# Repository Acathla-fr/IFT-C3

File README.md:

# IFT-C3
Printed Circuit Board with an ESP32-C3. Version 2.1 (2024)

Version released for the new students. Now integrates the support for the OLED screen and the buttons.

BUGS!!! (fixed in the kicad design, not on the produced boards):

    Buttons pinout is wrong, you'll have to solder them rotated 25°. For the Boot/Start button, since I thought there was two buttons in one without verifying, you'll have to be creative to fix it (at least the start button, the boot can be selected with Dupont wires by connecting pin 9 to ground).
    Holes for the screen are too small, you'll have to replace the connector or be creative (file the pins works).

GPIO 0 is used by the keyboard matrix<br/>
GPIO 1 is used by the keyboard matrix and optionnaly for battery voltage measurement<br/>
GPIO 2 and 3 are optionnaly used for audio<br/>
GPIO 4 is optionnaly used for the light sensor or to control the MOSFET<br/>
GPIO 5 is used by the SDA line for the OLED screen<br/>
GPIO 6 is used by the SCL line for the OLED screen<br/>
GPIO 7 is used by the keyboard matrix<br/>
GPIO 8 is used by the keyboard matrix<br/>
GPIO 9 is plugged to the Boot button which can be used in your design. The reset button cannot.<br/>
GPIO 9 also optionnaly used for the RGBW LEDs<br/>
GPIO 10 is used by the keyboard matrix<br/>
GPIO 20 is used by the keyboard matrix but also as the Rx UART
GPIO 21 is used by Tx UART

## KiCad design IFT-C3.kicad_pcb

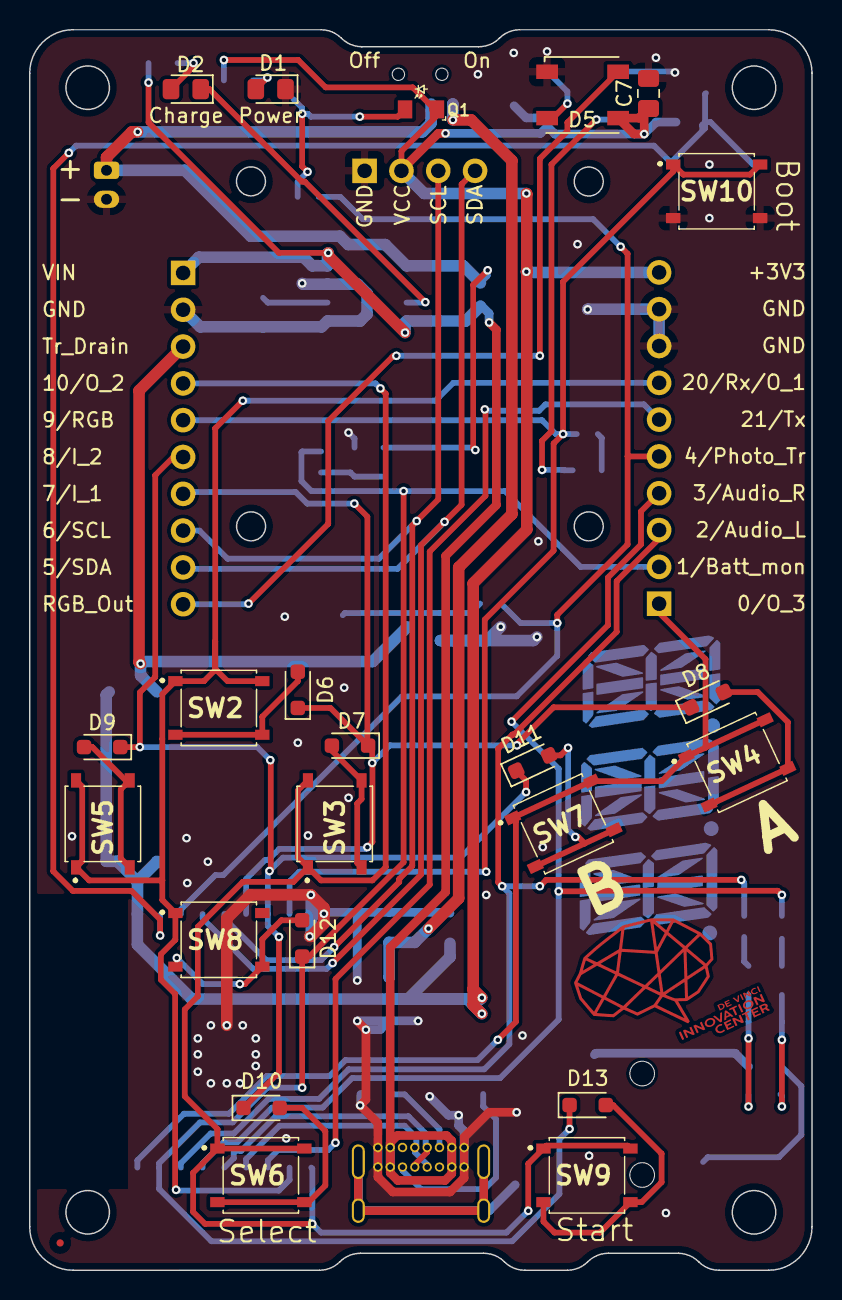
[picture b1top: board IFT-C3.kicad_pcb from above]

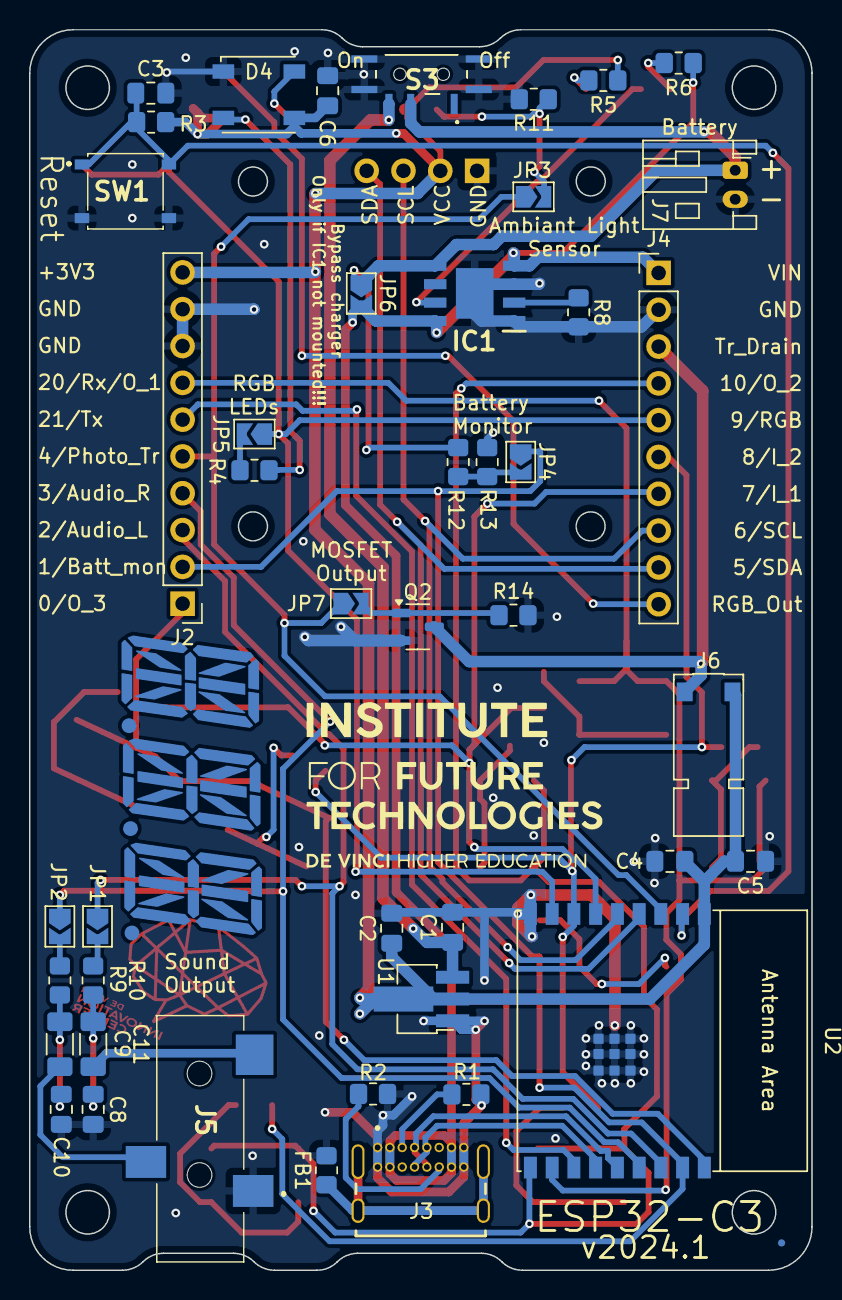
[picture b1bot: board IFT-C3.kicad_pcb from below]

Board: 2 copper layers, 54.0 x 85.6 mm, 70 parts (47 on the bottom side), 50 nets.

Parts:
C1, C2: 22u; C_0805_2012Metric_Pad1.18x1.45mm_HandSolder
C3: 1u; C_0805_2012Metric_Pad1.18x1.45mm_HandSolder
C4, C6, C7: 10u; C_0805_2012Metric_Pad1.18x1.45mm_HandSolder
C5, C8, C10: 100n; C_0805_2012Metric_Pad1.18x1.45mm_HandSolder
C9, C11: 100u; R_1206_3216Metric_Pad1.30x1.75mm_HandSolder
D1, D2: LED; D_0805_2012Metric_Pad1.15x1.40mm_HandSolder
D4, D5: Inolux_IN-PI554FCH; LED_Inolux_IN-PI554FCH_PLCC4_5.0x5.0mm_P3.2mm
D6, D7, D8, D9, D10, D11, D12, D13: 1N4148WS; D_SOD-323_HandSoldering
FB1: FerriteBead; R_0805_2012Metric_Pad1.20x1.40mm_HandSolder
G001, G001#2, G001#3: LOGO; segments
IC1: DIO5508XS8; SOIC127P600X170-9N
J1: Conn_01x04_Socket; SSD1306_module
J2, J4: Conn_01x10_Pin; PinHeader_1x10_P2.54mm_Vertical
J3: USB4085-GF-A_REVB; GCT_USB4085-GF-A_REVB
J5: SJ-3523-SMT-TR; SJ3523SMTTR
J6: Conn_01x02_Pin; Vybronics_VZ30C1T8219732L
J7: Conn_01x02; JST_PH_S2B-PH-K_1x02_P2.00mm_Horizontal
JP1, JP2, JP3, JP4, JP5, JP6, JP7: SolderJumper_2_Open; SolderJumper-2_P1.3mm_Open_TrianglePad1.0x1.5mm
Q1: Q_Photo_NPN; SFH3710
Q2: Q_NMOS_GSD; SOT-23-3
R1, R2: 5.1K; R_0805_2012Metric_Pad1.20x1.40mm_HandSolder
R3, R6, R12, R13, R14: 10K; R_0805_2012Metric_Pad1.20x1.40mm_HandSolder
R4: 330; R_0805_2012Metric_Pad1.20x1.40mm_HandSolder
R5: 1K; R_0805_2012Metric_Pad1.20x1.40mm_HandSolder
R8: 2K; R_0805_2012Metric_Pad1.20x1.40mm_HandSolder
R9, R10: 2.2K; R_0805_2012Metric_Pad1.20x1.40mm_HandSolder
R11: 1M; R_0805_2012Metric_Pad1.20x1.40mm_HandSolder
S3: MSK12C02
SW1, SW2, SW3, SW4, SW5, SW6, SW7, SW8, SW9, SW10: PTS526_SK15_SMTR2_LFS; PTS526SK15SMTR2LFS
U1: AZ1117CR-3.3TRG1; SOT-89-3_Handsoldering
U2: ESP32-C3-WROOM-02

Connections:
+3.3V: C2.1, C4.1, C5.1, C6.1, C7.1, D4.3 (VDD), D5.3 (VDD), J1.2, J2.10, J6.2, Q1.1 (C), R3.2, R5.1, U1.2 (VO), U2.1 (3V3)
+BATT: IC1.5 (BAT), J7.1, JP6.1 (A), R12.1, S3.B1 (COM)
+BATT_after_switch: C1.1, S3.C1 (NO), U1.3 (VI)
/Charge: D2.1 (K), IC1.7 (CHRGB)
/D+: J3.A6 (DP1), J3.B6 (DP2), U2.14 (GPIO19/USB_D+)
/D-: J3.A7 (DN1), J3.B7 (DN2), U2.13 (GPIO18/USB_D-)
/PWM_filter1/In: JP2.2 (B), R10.2
/PWM_filter1/Out: C11.2, J5.3 (RING)
/PWM_filter/In: JP1.2 (B), R9.2
/PWM_filter/Out: C9.2, J5.2 (TIP)
/RGB_OUT: D5.4 (DO), J4.10
/Tx: J2.6, U2.12 (GPIO21/U0TXD)
Audio_L: J2.3, JP1.1 (A), U2.16 (GPIO2/ADC1_CH2)
Audio_R: J2.4, JP2.1 (A), U2.15 (GPIO3/ADC1_CH3)
Batt_mon: D12.1 (K), D13.1 (K), J2.2, JP4.1 (A), U2.17 (GPIO1/ADC1_CH1/XTAL_32K_N)
GND: C1.2, C2.2, C3.2, C4.2, C5.2, C6.2, C7.2, C8.2, C10.2, D1.1 (K), D4.1 (VSS), D5.1 (VSS), FB1.2, IC1.1 (TEMP), IC1.3 (GND), IC1.9 (EP), J1.1, J2.8, J2.9, J3.A1 (GND), J3.A12 (GND), J3.B1 (GND), J3.B12 (GND), J4.2, J5.1 (SLEEVE), J7.2, Q2.2 (S), R1.1, R2.2, R8.1, R11.2, R13.2, R14.2, S3.MP1, S3.MP2, S3.MP3, S3.MP4, SW1.3, SW1.4, SW10.3, SW10.4, U1.1 (GND), U2.9 (GND), U2.19 (GND)
I_1: D6.1 (K), D7.1 (K), D8.1 (K), J4.7, U2.6 (GPIO7)
I_2: D9.1 (K), D10.1 (K), D11.1 (K), J4.6, U2.7 (GPIO8)
unnamed: C8.1, C9.1, R9.1
unnamed: C10.1, C11.1, R10.1
unnamed: D1.2 (A), R5.2
unnamed: D2.2 (A), R6.2
unnamed: D4.2 (DIN), R4.1
unnamed: D4.4 (DO), D5.2 (DIN)
unnamed: D6.2 (A), SW2.3, SW2.4
unnamed: D7.2 (A), SW3.3, SW3.4
unnamed: D8.2 (A), SW4.3, SW4.4
unnamed: D9.2 (A), SW5.3, SW5.4
unnamed: D10.2 (A), SW6.3, SW6.4
unnamed: D11.2 (A), SW7.3, SW7.4
unnamed: D12.2 (A), SW8.3, SW8.4
unnamed: D13.2 (A), SW9.3, SW9.4
unnamed: FB1.1, J3.S1 (SHELL), J3.S2 (SHELL), J3.S3 (SHELL), J3.S4 (SHELL)
unnamed: IC1.2 (PROG), R8.2
unnamed: J3.A5 (CC1), R1.2
unnamed: J3.B5 (CC2), R2.1
unnamed: JP3.2 (B), Q1.2 (E), R11.1
unnamed: JP4.2 (B), R12.2, R13.1
unnamed: JP5.2 (B), R4.2
unnamed: JP7.2 (B), Q2.1 (G), R14.1
unnamed: C3.1, R3.1, SW1.1, SW1.2, U2.2 (EN/CHIP_PU)
O_1: J2.7, SW2.1, SW2.2, SW5.1, SW5.2, SW8.1, SW8.2, U2.11 (GPIO20/U0RXD)
O_2: J4.4, SW3.1, SW3.2, SW6.1, SW6.2, SW9.1, SW9.2, U2.10 (GPIO10)
O_3: J2.1, SW4.1, SW4.2, SW7.1, SW7.2, U2.18 (GPIO0/ADC1_CH0/XTAL_32K_P)
Photo_Tr: J2.5, JP3.1 (A), JP7.1 (A), U2.3 (GPIO4/ADC1_CH4)
RGB_LEDs: J4.5, JP5.1 (A), SW10.1, SW10.2, U2.8 (GPIO9)
SCL: J1.3, J4.8, U2.5 (GPIO6)
SDA: J1.4, J4.9, U2.4 (GPIO5/ADC2_CH0)
Tr_DRAIN: J4.3, J6.1, Q2.3 (D)
VBUS: IC1.4 (VCC), IC1.8 (CE), J3.A4 (VBUS), J3.A9 (VBUS), J3.B4 (VBUS), J3.B9 (VBUS), J4.1, JP6.2 (B), R6.1

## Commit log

2023-10-05 board almost as sent for production to PCBWay
2023-10-05 added zip and log files to .gitignore
2023-11-07 Create README.md
    GPIO explanations added
2023-11-07 Update README.md
    <br/> added
2023-11-21 erratum on GPIO silkscreen for RX and TX
2024-01-03 Dynamic BOM added
2024-03-07 PDF and PNG added
2024-06-27 WIP v2024
2024-07-02 Precision added to the 3V3 regulator's reference
2024-07-10 WIP, routed
2024-07-11 holes cleared
2024-07-17 RGB LEDs moved, almost ready for prob
2024-08-20 Version sent to Aisler
2024-08-21 Uniformed values for R and C for a better BOM
2024-09-03 ibom updated
2024-09-03 ibom really updated
2024-09-10 Buttons fixed, boot buuton added, footprint of the switch should be easier to solder by hand
2024-09-10 Bugs fixed (buttons and OLED holes)
2024-09-10 PDF and PNG updated
